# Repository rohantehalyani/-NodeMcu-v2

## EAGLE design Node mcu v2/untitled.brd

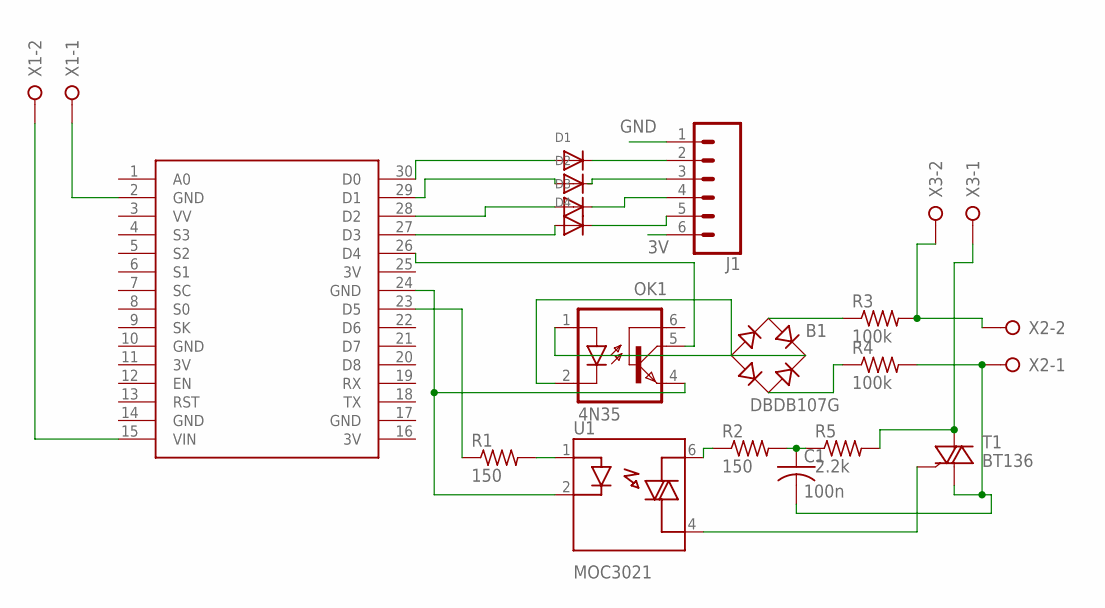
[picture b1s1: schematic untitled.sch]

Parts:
B1: DBDB107G; DB
C1: 100n; C050-045X075
D1, D2, D3, D4: DIODEDO-1N4148; DO-1N4148
J1: CONN_06LONGPADS; 1X06_LONGPADS
OK1: 4N35; DIL06
R1, R2: 150; 0207/10
R3, R4: 100k; 0207/10
R5: 2.2k; 0207/10
T1: BT136; TO220AB
U1: MOC3021; DIP762W45P254L889H508Q6
U$1: NODEMCU
X1, X2, X3: W237-02P; W237-132

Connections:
3V: J1.6, U$1.11 (3V), U$1.16 (3V), U$1.25 (3V)
GND: J1.1, U$1.10 (GND), U$1.14 (GND), U$1.17 (GND)
unnamed: D1.A, U$1.30 (D0)
unnamed: D4.A, U$1.27 (D3)
unnamed: D3.A, U$1.28 (D2)
unnamed: R3.2, X2.2, X3.2
unnamed: D3.C, J1.4
unnamed: U$1.15 (VIN), X1.2
unnamed: D4.C, J1.5
unnamed: D1.C, J1.2
unnamed: U$1.2 (GND), X1.1
unnamed: D2.A, U$1.29 (D1)
unnamed: D2.C, J1.3
unnamed: B1.AC1, R3.1
unnamed: B1.AC2, R4.1
unnamed: T1.3 (G), U1.4 (MAIN_TERM2)
unnamed: B1.-, OK1.2 (C)
unnamed: B1.+, OK1.1 (A)
unnamed: OK1.4 (EMI), U1.2 (CATODE), U$1.24 (GND)
unnamed: OK1.5 (COL), U$1.26 (D4)
unnamed: R1.1, U$1.23 (D5)
unnamed: R1.2, U1.1 (ANODE)
unnamed: R2.1, U1.6 (MAIN_TERM1)
unnamed: C1.1, R2.2, R5.1
unnamed: R5.2, T1.2 (A2), X3.1
unnamed: C1.2, R4.2, T1.1 (A1), X2.1

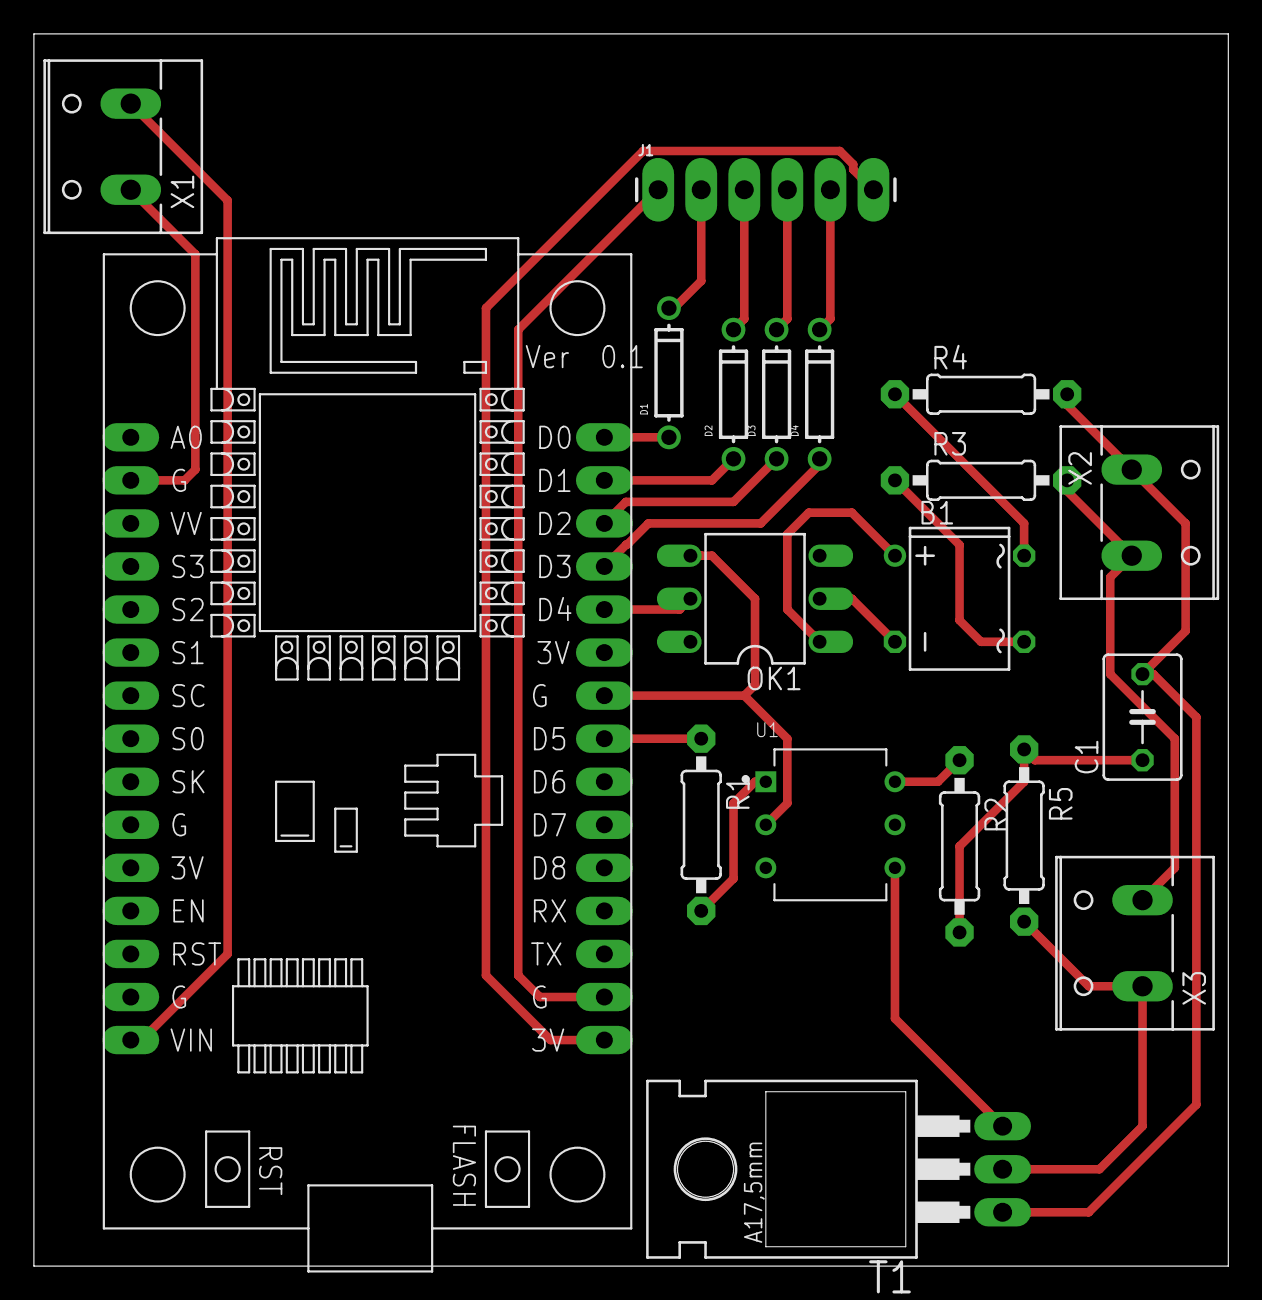
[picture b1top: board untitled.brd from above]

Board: 2 copper layers, 70.5 x 72.7 mm, 19 parts (0 on the bottom side), 26 nets.

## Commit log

2020-07-23 with fan speed controller

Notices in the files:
parts and their libraries:
SparkFun-Connectors: Licensing: Creative Commons ShareAlike 4.0 International - https://creativecommons.org/licenses/by-sa/4.0
